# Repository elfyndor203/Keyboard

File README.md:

# Keyboard
Keyboard with alt to the right

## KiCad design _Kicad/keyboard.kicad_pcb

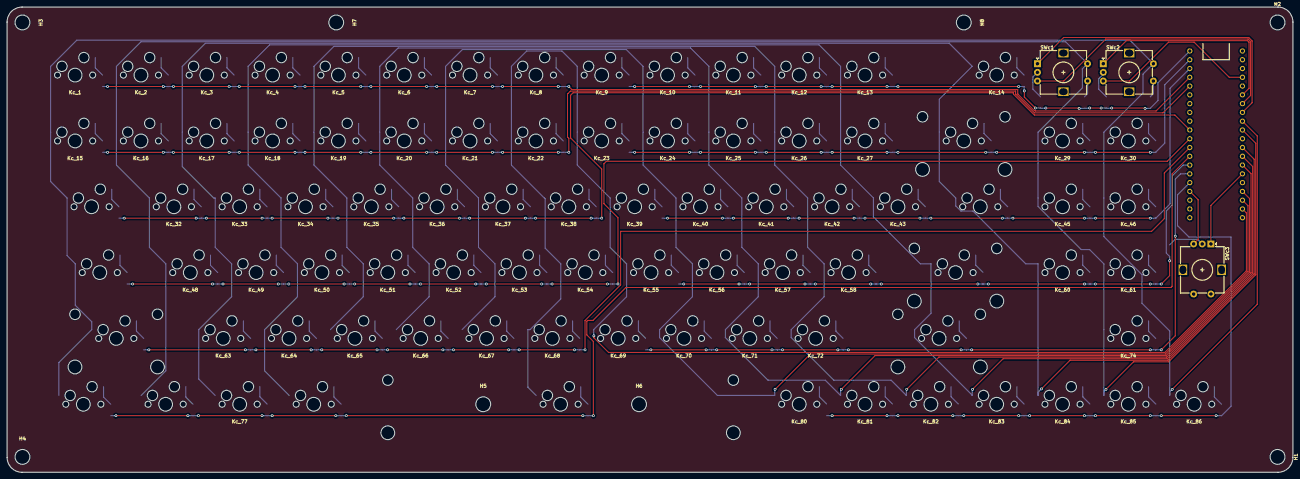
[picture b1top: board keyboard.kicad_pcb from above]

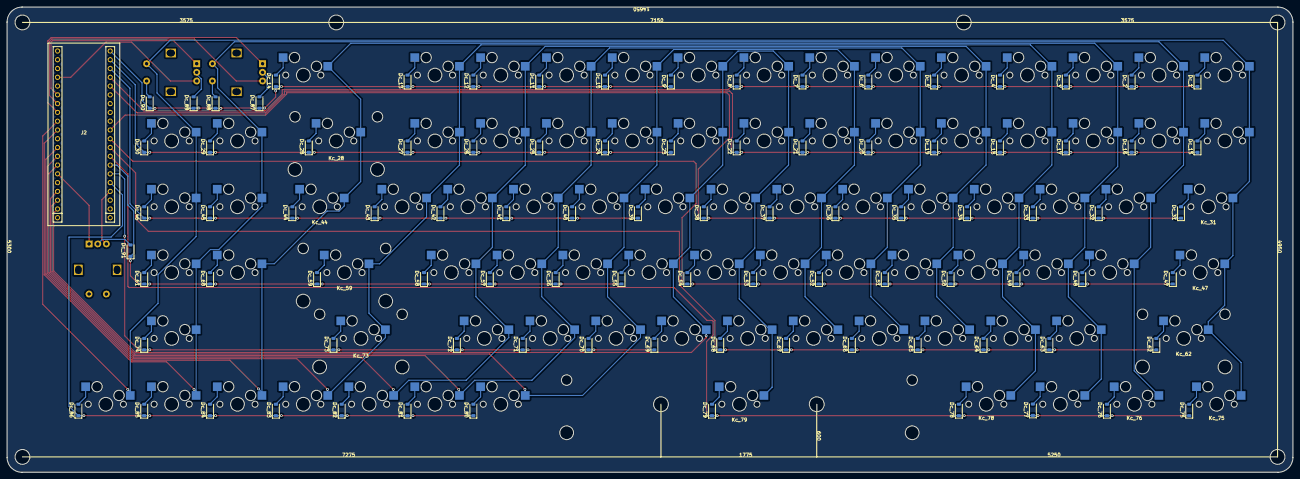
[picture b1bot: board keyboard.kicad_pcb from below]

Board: 2 copper layers, 372.1 x 134.6 mm, 189 parts (92 on the bottom side), 117 nets.

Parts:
Dc_1, Dc_2, Dc_3, Dc_4, Dc_5, Dc_6, Dc_7, Dc_8, Dc_9, Dc_10, Dc_11, Dc_12, Dc_13, Dc_14, Dc_15, Dc_16, Dc_17, Dc_18, Dc_19, Dc_20, Dc_21, Dc_22, Dc_23, Dc_24, Dc_25, Dc_26, Dc_27, Dc_28, Dc_29, Dc_30, Dc_31, Dc_32, Dc_33, Dc_34, Dc_35, Dc_36, Dc_37, Dc_38, Dc_39, Dc_40, Dc_41, Dc_42, Dc_43, Dc_44, Dc_45, Dc_46, Dc_47, Dc_48, Dc_49, Dc_50, Dc_51, Dc_52, Dc_53, Dc_54, Dc_55, Dc_56, Dc_57, Dc_58, Dc_59, Dc_60, Dc_61, Dc_62, Dc_63, Dc_64, Dc_65, Dc_66, Dc_67, Dc_68, Dc_69, Dc_70, Dc_71, Dc_72, Dc_73, Dc_74, Dc_75, Dc_76, Dc_77, Dc_78, Dc_79, Dc_80, Dc_81, Dc_82, Dc_83, Dc_84, Dc_85, Dc_86, Dc_87, Dc_88, Dc_89, Dc_90, Dc_91: D; D_SOD-123
H1, H2, H3, H4, H5, H6, H7, H8: MountingHole; MountingHole_4.3mm_M4
J2: Conn_02x20_Top_Bottom; blackpill
Kc_1, Kc_2, Kc_3, Kc_4, Kc_5, Kc_6, Kc_7, Kc_8, Kc_9, Kc_10, Kc_11, Kc_12, Kc_13, Kc_14, Kc_15, Kc_16, Kc_17, Kc_18, Kc_19, Kc_20, Kc_21, Kc_22, Kc_23, Kc_24, Kc_25, Kc_26, Kc_27, Kc_29, Kc_30, Kc_32, Kc_33, Kc_34, Kc_35, Kc_36, Kc_37, Kc_38, Kc_39, Kc_40, Kc_41, Kc_42, Kc_43, Kc_45, Kc_46, Kc_48, Kc_49, Kc_50, Kc_51, Kc_52, Kc_53, Kc_54, Kc_55, Kc_56, Kc_57, Kc_58, Kc_60, Kc_61, Kc_63, Kc_64, Kc_65, Kc_66, Kc_67, Kc_68, Kc_69, Kc_70, Kc_71, Kc_72, Kc_74, Kc_77, Kc_80, Kc_81, Kc_82, Kc_83, Kc_84, Kc_85, Kc_86: KEYSW; MXOnly-1U-Hotswap
Kc_28: KEYSW; MXOnly-2U-Hotswap
Kc_31, Kc_44: KEYSW; MXOnly-1.5U-Hotswap
Kc_47: KEYSW; MXOnly-1.75U-Hotswap
Kc_59, Kc_62: KEYSW; MXOnly-2.25U-Hotswap
Kc_73: KEYSW; MXOnly-2.75U-Hotswap
Kc_75, Kc_76, Kc_78: KEYSW; MXOnly-1.25U-Hotswap
Kc_79: KEYSW; MXOnly-6.25U-Hotswap
SWc1, SWc2, SWc3: RotaryEncoder_Switch; RotaryEncoder_Alps_EC12E-Switch_Vertical_H20mm

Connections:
/12x8/COL1: J2.9, Kc_1.1 (COL), Kc_15.1 (COL), Kc_30.1 (COL), Kc_31.1 (COL), Kc_46.1 (COL), Kc_47.1 (COL), Kc_62.1 (COL), Kc_75.1 (COL), Kc_86.1 (COL), SWc2.S1
/12x8/COL2: J2.10, Kc_2.1 (COL), Kc_16.1 (COL), Kc_29.1 (COL), Kc_32.1 (COL), Kc_45.1 (COL), Kc_48.1 (COL), Kc_61.1 (COL), Kc_74.1 (COL), Kc_76.1 (COL), Kc_85.1 (COL), SWc1.S1
/12x8/COL3: J2.12, Kc_3.1 (COL), Kc_14.1 (COL), Kc_17.1 (COL), Kc_28.1 (COL), Kc_33.1 (COL), Kc_44.1 (COL), Kc_49.1 (COL), Kc_60.1 (COL), Kc_63.1 (COL), Kc_77.1 (COL), Kc_84.1 (COL)
/12x8/COL4: J2.13, Kc_4.1 (COL), Kc_13.1 (COL), Kc_18.1 (COL), Kc_27.1 (COL), Kc_34.1 (COL), Kc_43.1 (COL), Kc_50.1 (COL), Kc_59.1 (COL), Kc_64.1 (COL), Kc_73.1 (COL), Kc_78.1 (COL), Kc_83.1 (COL)
/12x8/COL5: J2.14, Kc_5.1 (COL), Kc_12.1 (COL), Kc_19.1 (COL), Kc_26.1 (COL), Kc_35.1 (COL), Kc_42.1 (COL), Kc_51.1 (COL), Kc_58.1 (COL), Kc_65.1 (COL), Kc_72.1 (COL), Kc_82.1 (COL)
/12x8/COL6: J2.17, Kc_6.1 (COL), Kc_11.1 (COL), Kc_20.1 (COL), Kc_25.1 (COL), Kc_36.1 (COL), Kc_41.1 (COL), Kc_52.1 (COL), Kc_57.1 (COL), Kc_66.1 (COL), Kc_71.1 (COL), Kc_81.1 (COL)
/12x8/COL7: J2.18, Kc_7.1 (COL), Kc_10.1 (COL), Kc_21.1 (COL), Kc_24.1 (COL), Kc_37.1 (COL), Kc_40.1 (COL), Kc_53.1 (COL), Kc_56.1 (COL), Kc_67.1 (COL), Kc_70.1 (COL), Kc_80.1 (COL)
/12x8/COL8: J2.19, Kc_8.1 (COL), Kc_9.1 (COL), Kc_22.1 (COL), Kc_23.1 (COL), Kc_38.1 (COL), Kc_39.1 (COL), Kc_54.1 (COL), Kc_55.1 (COL), Kc_68.1 (COL), Kc_69.1 (COL), Kc_79.1 (COL)
/12x8/ROT1A: J2.8, SWc1.A
/12x8/ROT1B: J2.7, SWc1.B
/12x8/ROT2A: J2.6, SWc2.A
/12x8/ROT2B: J2.4, SWc2.B
/12x8/ROT3A: J2.15, SWc3.A
/12x8/ROT3B: J2.37, SWc3.B
/12x8/ROW1: Dc_1.1 (K), Dc_2.1 (K), Dc_3.1 (K), Dc_4.1 (K), Dc_5.1 (K), Dc_6.1 (K), Dc_7.1 (K), Dc_8.1 (K), J2.24
/12x8/ROW2: Dc_9.1 (K), Dc_10.1 (K), Dc_11.1 (K), Dc_12.1 (K), Dc_13.1 (K), Dc_14.1 (K), Dc_87.1 (K), Dc_88.1 (K), Dc_89.1 (K), Dc_90.1 (K), J2.21
/12x8/ROW3: Dc_15.1 (K), Dc_16.1 (K), Dc_17.1 (K), Dc_18.1 (K), Dc_19.1 (K), Dc_20.1 (K), Dc_21.1 (K), Dc_22.1 (K), J2.25
/12x8/ROW4: Dc_23.1 (K), Dc_24.1 (K), Dc_25.1 (K), Dc_26.1 (K), Dc_27.1 (K), Dc_28.1 (K), Dc_29.1 (K), Dc_30.1 (K), J2.22
/12x8/ROW5: Dc_31.1 (K), Dc_32.1 (K), Dc_33.1 (K), Dc_34.1 (K), Dc_35.1 (K), Dc_36.1 (K), Dc_37.1 (K), Dc_38.1 (K), J2.30
/12x8/ROW6: Dc_39.1 (K), Dc_40.1 (K), Dc_41.1 (K), Dc_42.1 (K), Dc_43.1 (K), Dc_44.1 (K), Dc_45.1 (K), Dc_46.1 (K), J2.23
/12x8/ROW7: Dc_47.1 (K), Dc_48.1 (K), Dc_49.1 (K), Dc_50.1 (K), Dc_51.1 (K), Dc_52.1 (K), Dc_53.1 (K), Dc_54.1 (K), J2.31
/12x8/ROW8: Dc_55.1 (K), Dc_56.1 (K), Dc_57.1 (K), Dc_58.1 (K), Dc_59.1 (K), Dc_60.1 (K), Dc_61.1 (K), Dc_91.1 (K), J2.34
/12x8/ROW9: Dc_62.1 (K), Dc_63.1 (K), Dc_64.1 (K), Dc_65.1 (K), Dc_66.1 (K), Dc_67.1 (K), Dc_68.1 (K), J2.32
/12x8/ROW10: Dc_69.1 (K), Dc_70.1 (K), Dc_71.1 (K), Dc_72.1 (K), Dc_73.1 (K), Dc_74.1 (K), J2.35
/12x8/ROW11: Dc_75.1 (K), Dc_76.1 (K), Dc_77.1 (K), Dc_78.1 (K), Dc_79.1 (K), J2.33
/12x8/ROW12: Dc_80.1 (K), Dc_81.1 (K), Dc_82.1 (K), Dc_83.1 (K), Dc_84.1 (K), Dc_85.1 (K), Dc_86.1 (K), J2.36
unnamed: Dc_1.2 (A), Kc_1.2 (ROW)
unnamed: Dc_2.2 (A), Kc_2.2 (ROW)
unnamed: Dc_3.2 (A), Kc_3.2 (ROW)
unnamed: Dc_4.2 (A), Kc_4.2 (ROW)
unnamed: Dc_5.2 (A), Kc_5.2 (ROW)
unnamed: Dc_6.2 (A), Kc_6.2 (ROW)
unnamed: Dc_7.2 (A), Kc_7.2 (ROW)
unnamed: Dc_8.2 (A), Kc_8.2 (ROW)
unnamed: Dc_9.2 (A), Kc_9.2 (ROW)
unnamed: Dc_10.2 (A), Kc_10.2 (ROW)
unnamed: Dc_11.2 (A), Kc_11.2 (ROW)
unnamed: Dc_12.2 (A), Kc_12.2 (ROW)
unnamed: Dc_13.2 (A), Kc_13.2 (ROW)
unnamed: Dc_14.2 (A), Kc_14.2 (ROW)
unnamed: Dc_15.2 (A), Kc_15.2 (ROW)
unnamed: Dc_16.2 (A), Kc_16.2 (ROW)
unnamed: Dc_17.2 (A), Kc_17.2 (ROW)
unnamed: Dc_18.2 (A), Kc_18.2 (ROW)
unnamed: Dc_19.2 (A), Kc_19.2 (ROW)
unnamed: Dc_20.2 (A), Kc_20.2 (ROW)
unnamed: Dc_21.2 (A), Kc_21.2 (ROW)
unnamed: Dc_22.2 (A), Kc_22.2 (ROW)
unnamed: Dc_23.2 (A), Kc_23.2 (ROW)
unnamed: Dc_24.2 (A), Kc_24.2 (ROW)
unnamed: Dc_25.2 (A), Kc_25.2 (ROW)
unnamed: Dc_26.2 (A), Kc_26.2 (ROW)
unnamed: Dc_27.2 (A), Kc_27.2 (ROW)
unnamed: Dc_28.2 (A), Kc_28.2 (ROW)
unnamed: Dc_29.2 (A), Kc_29.2 (ROW)
unnamed: Dc_30.2 (A), Kc_30.2 (ROW)
unnamed: Dc_31.2 (A), Kc_31.2 (ROW)
unnamed: Dc_32.2 (A), Kc_32.2 (ROW)
unnamed: Dc_33.2 (A), Kc_33.2 (ROW)
unnamed: Dc_34.2 (A), Kc_34.2 (ROW)
unnamed: Dc_35.2 (A), Kc_35.2 (ROW)
unnamed: Dc_36.2 (A), Kc_36.2 (ROW)
unnamed: Dc_37.2 (A), Kc_37.2 (ROW)
unnamed: Dc_38.2 (A), Kc_38.2 (ROW)
unnamed: Dc_39.2 (A), Kc_39.2 (ROW)
unnamed: Dc_40.2 (A), Kc_40.2 (ROW)
unnamed: Dc_41.2 (A), Kc_41.2 (ROW)
unnamed: Dc_42.2 (A), Kc_42.2 (ROW)
unnamed: Dc_43.2 (A), Kc_43.2 (ROW)
unnamed: Dc_44.2 (A), Kc_44.2 (ROW)
unnamed: Dc_45.2 (A), Kc_45.2 (ROW)
unnamed: Dc_46.2 (A), Kc_46.2 (ROW)
unnamed: Dc_47.2 (A), Kc_47.2 (ROW)
unnamed: Dc_48.2 (A), Kc_48.2 (ROW)
unnamed: Dc_49.2 (A), Kc_49.2 (ROW)
unnamed: Dc_50.2 (A), Kc_50.2 (ROW)
unnamed: Dc_51.2 (A), Kc_51.2 (ROW)
unnamed: Dc_52.2 (A), Kc_52.2 (ROW)
unnamed: Dc_53.2 (A), Kc_53.2 (ROW)
unnamed: Dc_54.2 (A), Kc_54.2 (ROW)
unnamed: Dc_55.2 (A), Kc_55.2 (ROW)
unnamed: Dc_56.2 (A), Kc_56.2 (ROW)
unnamed: Dc_57.2 (A), Kc_57.2 (ROW)
unnamed: Dc_58.2 (A), Kc_58.2 (ROW)
unnamed: Dc_59.2 (A), Kc_59.2 (ROW)
unnamed: Dc_60.2 (A), Kc_60.2 (ROW)
unnamed: Dc_61.2 (A), Kc_61.2 (ROW)
unnamed: Dc_62.2 (A), Kc_62.2 (ROW)
unnamed: Dc_63.2 (A), Kc_63.2 (ROW)
unnamed: Dc_64.2 (A), Kc_64.2 (ROW)
unnamed: Dc_65.2 (A), Kc_65.2 (ROW)
unnamed: Dc_66.2 (A), Kc_66.2 (ROW)
unnamed: Dc_67.2 (A), Kc_67.2 (ROW)
unnamed: Dc_68.2 (A), Kc_68.2 (ROW)
unnamed: Dc_69.2 (A), Kc_69.2 (ROW)
unnamed: Dc_70.2 (A), Kc_70.2 (ROW)
unnamed: Dc_71.2 (A), Kc_71.2 (ROW)
unnamed: Dc_72.2 (A), Kc_72.2 (ROW)
unnamed: Dc_73.2 (A), Kc_73.2 (ROW)
unnamed: Dc_74.2 (A), Kc_74.2 (ROW)
unnamed: Dc_75.2 (A), Kc_75.2 (ROW)
unnamed: Dc_76.2 (A), Kc_76.2 (ROW)
unnamed: Dc_77.2 (A), Kc_77.2 (ROW)
unnamed: Dc_78.2 (A), Kc_78.2 (ROW)
unnamed: Dc_79.2 (A), Kc_79.2 (ROW)
unnamed: Dc_80.2 (A), Kc_80.2 (ROW)
unnamed: Dc_81.2 (A), Kc_81.2 (ROW)
unnamed: Dc_82.2 (A), Kc_82.2 (ROW)
unnamed: Dc_83.2 (A), Kc_83.2 (ROW)
unnamed: Dc_84.2 (A), Kc_84.2 (ROW)
unnamed: Dc_85.2 (A), Kc_85.2 (ROW)
unnamed: Dc_86.2 (A), Kc_86.2 (ROW)
unnamed: Dc_87.2 (A), SWc1.C
unnamed: Dc_88.2 (A), SWc1.S2
unnamed: Dc_89.2 (A), SWc2.C
unnamed: Dc_90.2 (A), SWc2.S2
unnamed: Dc_91.2 (A), SWc3.C

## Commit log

2024-12-25 kicad update
2024-12-25 ai03 libraries into kicad
2024-12-25 rotary encoder and hotswap switch footprints
2024-12-25 all key switches checkpoint
2024-12-25 started custom pcb
2024-12-25 wired custom pcb, need blackpill footprint
2024-12-25 blackpill footprint added
2024-12-26 wiring done, controller not placed
2025-01-03 pcb diodes and keys arranged
2025-01-05 swapped diodes to front
2025-01-05 routed tracks and fixed accidental intersection near R1
2025-02-02 stable but not enough pins
2025-02-26 need to flip pcb and fix footprint
2025-03-16 fully done with fab no logo
2025-03-27 reorganizationgit add .
